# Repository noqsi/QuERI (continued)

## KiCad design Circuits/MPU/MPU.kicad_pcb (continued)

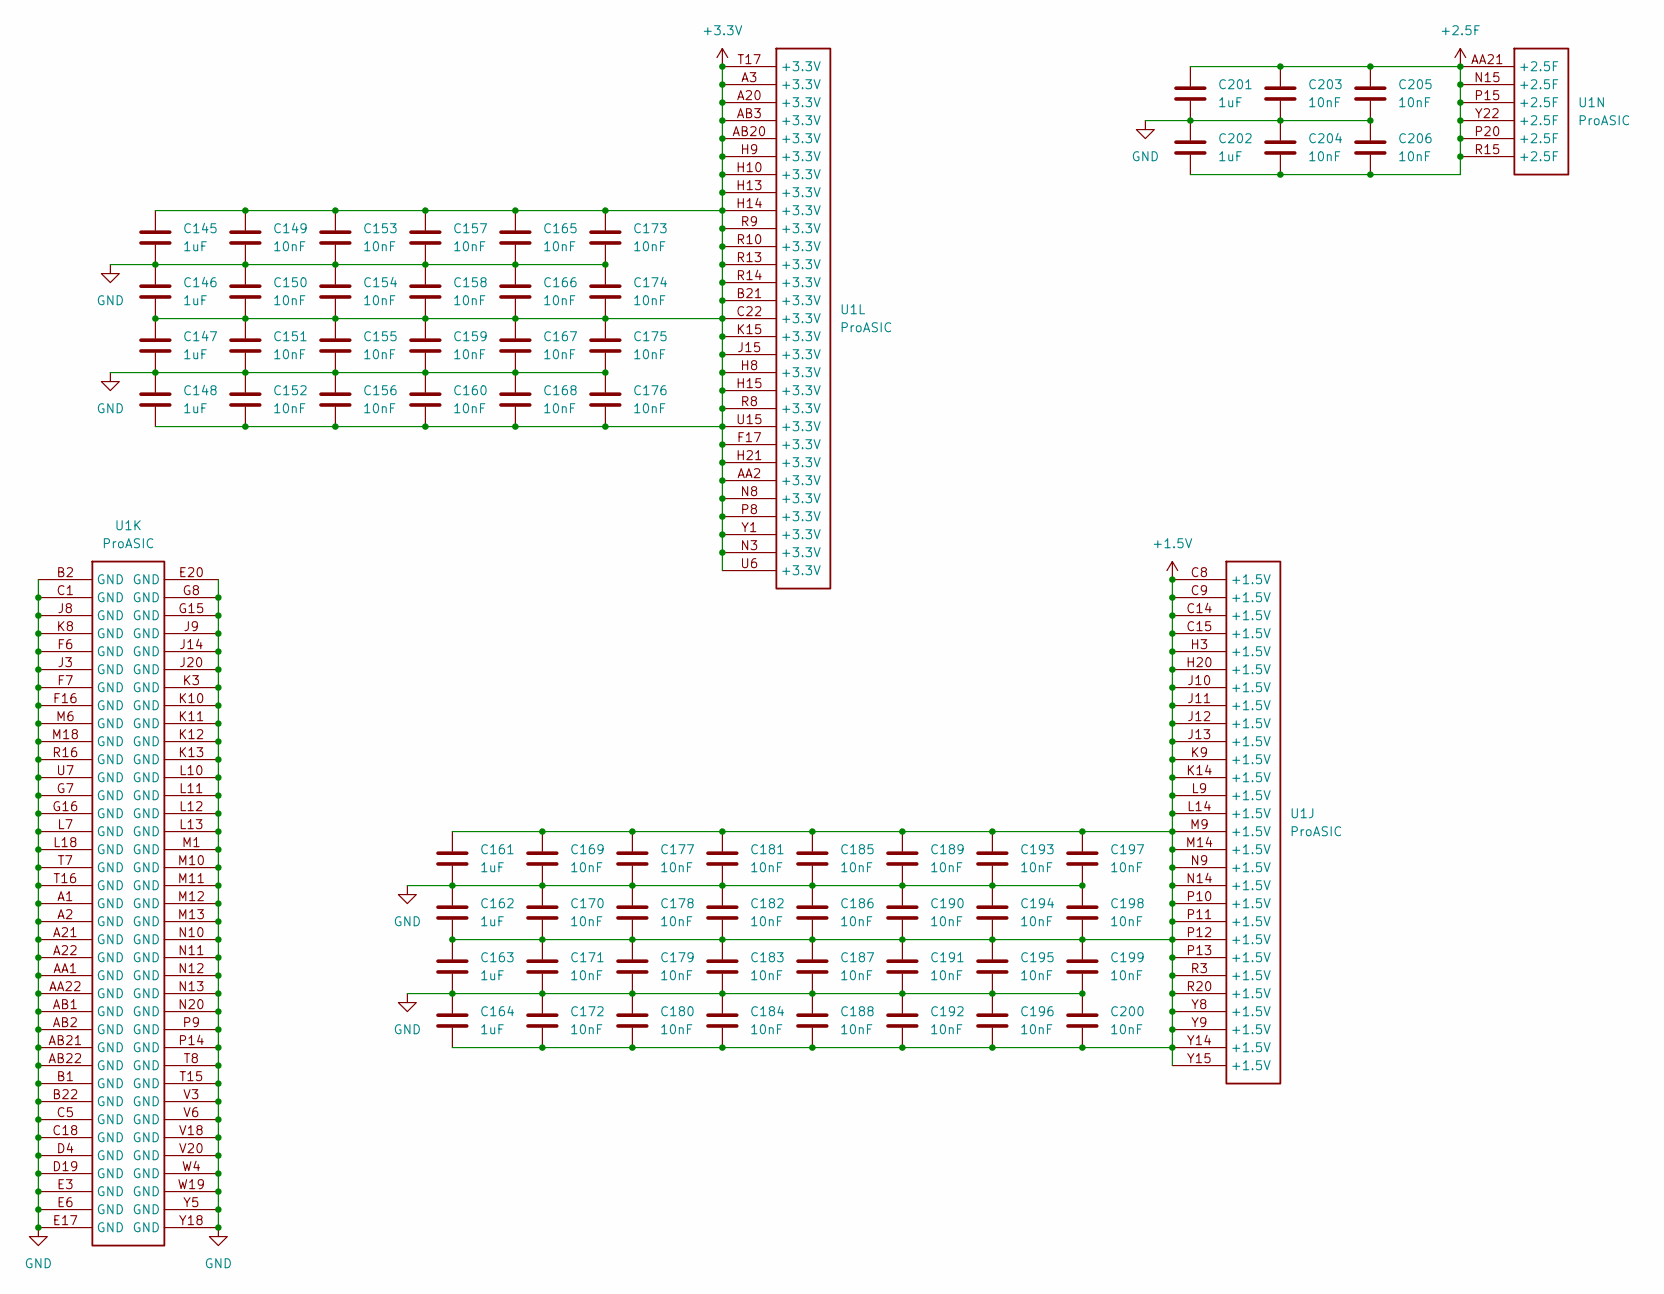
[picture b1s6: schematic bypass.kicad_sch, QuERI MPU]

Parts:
C145, C146, C147, C148, C161, C162, C163, C164, C201, C202: 1uF; C_0805_2012Metric
C149, C150, C151, C152, C153, C154, C155, C156, C157, C158, C159, C160, C165, C166, C167, C168, C169, C170, C171, C172, C173, C174, C175, C176, C177, C178, C179, C180, C181, C182, C183, C184, C185, C186, C187, C188, C189, C190, C191, C192, C193, C194, C195, C196, C197, C198, C199, C200, C203, C204, C205, C206: 10nF; C_0603_1608Metric
U1: ProASIC; BGA-484_23.0x23.0mm_Layout22x22_P1.0mm

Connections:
+1.5V: C161.1, C162.2, C163.1, C164.2, C169.1, C170.2, C171.1, C172.2, C177.1, C178.2, C179.1, C180.2, C181.1, C182.2, C183.1, C184.2, C185.1, C186.2, C187.1, C188.2, C189.1, C190.2, C191.1, C192.2, C193.1, C194.2, C195.1, C196.2, C197.1, C198.2, C199.1, C200.2, U1.C8 (+1.5V), U1.C9 (+1.5V), U1.C14 (+1.5V), U1.C15 (+1.5V), U1.H3 (+1.5V), U1.H20 (+1.5V), U1.J10 (+1.5V), U1.J11 (+1.5V), U1.J12 (+1.5V), U1.J13 (+1.5V), U1.K9 (+1.5V), U1.K14 (+1.5V), U1.L9 (+1.5V), U1.L14 (+1.5V), U1.M9 (+1.5V), U1.M14 (+1.5V), U1.N9 (+1.5V), U1.N14 (+1.5V), U1.P10 (+1.5V), U1.P11 (+1.5V), U1.P12 (+1.5V), U1.P13 (+1.5V), U1.R3 (+1.5V), U1.R20 (+1.5V), U1.Y8 (+1.5V), U1.Y9 (+1.5V), U1.Y14 (+1.5V), U1.Y15 (+1.5V); also elsewhere on the board
+2.5F: C201.1, C202.2, C203.1, C204.2, C205.1, C206.2, U1.AA21 (+2.5F), U1.N15 (+2.5F), U1.P15 (+2.5F), U1.P20 (+2.5F), U1.R15 (+2.5F), U1.Y22 (+2.5F); also elsewhere on the board
+3.3V: C145.1, C146.2, C147.1, C148.2, C149.1, C150.2, C151.1, C152.2, C153.1, C154.2, C155.1, C156.2, C157.1, C158.2, C159.1, C160.2, C165.1, C166.2, C167.1, C168.2, C173.1, C174.2, C175.1, C176.2, U1.A3 (+3.3V), U1.A20 (+3.3V), U1.AA2 (+3.3V), U1.AB3 (+3.3V), U1.AB20 (+3.3V), U1.B21 (+3.3V), U1.C22 (+3.3V), U1.F17 (+3.3V), U1.H8 (+3.3V), U1.H9 (+3.3V), U1.H10 (+3.3V), U1.H13 (+3.3V), U1.H14 (+3.3V), U1.H15 (+3.3V), U1.H21 (+3.3V), U1.J15 (+3.3V), U1.K15 (+3.3V), U1.N3 (+3.3V), U1.N8 (+3.3V), U1.P8 (+3.3V), U1.R8 (+3.3V), U1.R9 (+3.3V), U1.R10 (+3.3V), U1.R13 (+3.3V), U1.R14 (+3.3V), U1.T17 (+3.3V), U1.U6 (+3.3V), U1.U15 (+3.3V), U1.Y1 (+3.3V); also elsewhere on the board
GND: C145.2, C146.1, C147.2, C148.1, C149.2, C150.1, C151.2, C152.1, C153.2, C154.1, C155.2, C156.1, C157.2, C158.1, C159.2, C160.1, C161.2, C162.1, C163.2, C164.1, C165.2, C166.1, C167.2, C168.1, C169.2, C170.1, C171.2, C172.1, C173.2, C174.1, C175.2, C176.1, C177.2, C178.1, C179.2, C180.1, C181.2, C182.1, C183.2, C184.1, C185.2, C186.1, C187.2, C188.1, C189.2, C190.1, C191.2, C192.1, C193.2, C194.1, C195.2, C196.1, C197.2, C198.1, C199.2, C200.1, C201.2, C202.1, C203.2, C204.1, C205.2, C206.1, U1.A1 (GND), U1.A2 (GND), U1.A21 (GND), U1.A22 (GND), U1.AA1 (GND), U1.AA22 (GND), U1.AB1 (GND), U1.AB2 (GND), U1.AB21 (GND), U1.AB22 (GND), U1.B1 (GND), U1.B2 (GND), U1.B22 (GND), U1.C1 (GND), U1.C5 (GND), U1.C18 (GND), U1.D4 (GND), U1.D19 (GND), U1.E3 (GND), U1.E6 (GND), U1.E17 (GND), U1.E20 (GND), U1.F6 (GND), U1.F7 (GND), U1.F16 (GND), U1.G7 (GND), U1.G8 (GND), U1.G15 (GND), U1.G16 (GND), U1.J3 (GND), U1.J8 (GND), U1.J9 (GND), U1.J14 (GND), U1.J20 (GND), U1.K3 (GND), U1.K8 (GND), U1.K10 (GND), U1.K11 (GND), U1.K12 (GND), U1.K13 (GND), U1.L7 (GND), U1.L10 (GND), U1.L11 (GND), U1.L12 (GND), U1.L13 (GND), U1.L18 (GND), U1.M1 (GND), U1.M6 (GND), U1.M10 (GND), U1.M11 (GND), U1.M12 (GND), U1.M13 (GND), U1.M18 (GND), U1.N10 (GND), U1.N11 (GND), U1.N12 (GND), U1.N13 (GND), U1.N20 (GND), U1.P9 (GND), U1.P14 (GND), U1.R16 (GND), U1.T7 (GND), U1.T8 (GND), U1.T15 (GND), U1.T16 (GND), U1.U7 (GND), U1.V3 (GND), U1.V6 (GND), U1.V18 (GND), U1.V20 (GND), U1.W4 (GND), U1.W19 (GND), U1.Y5 (GND), U1.Y18 (GND); also elsewhere on the board

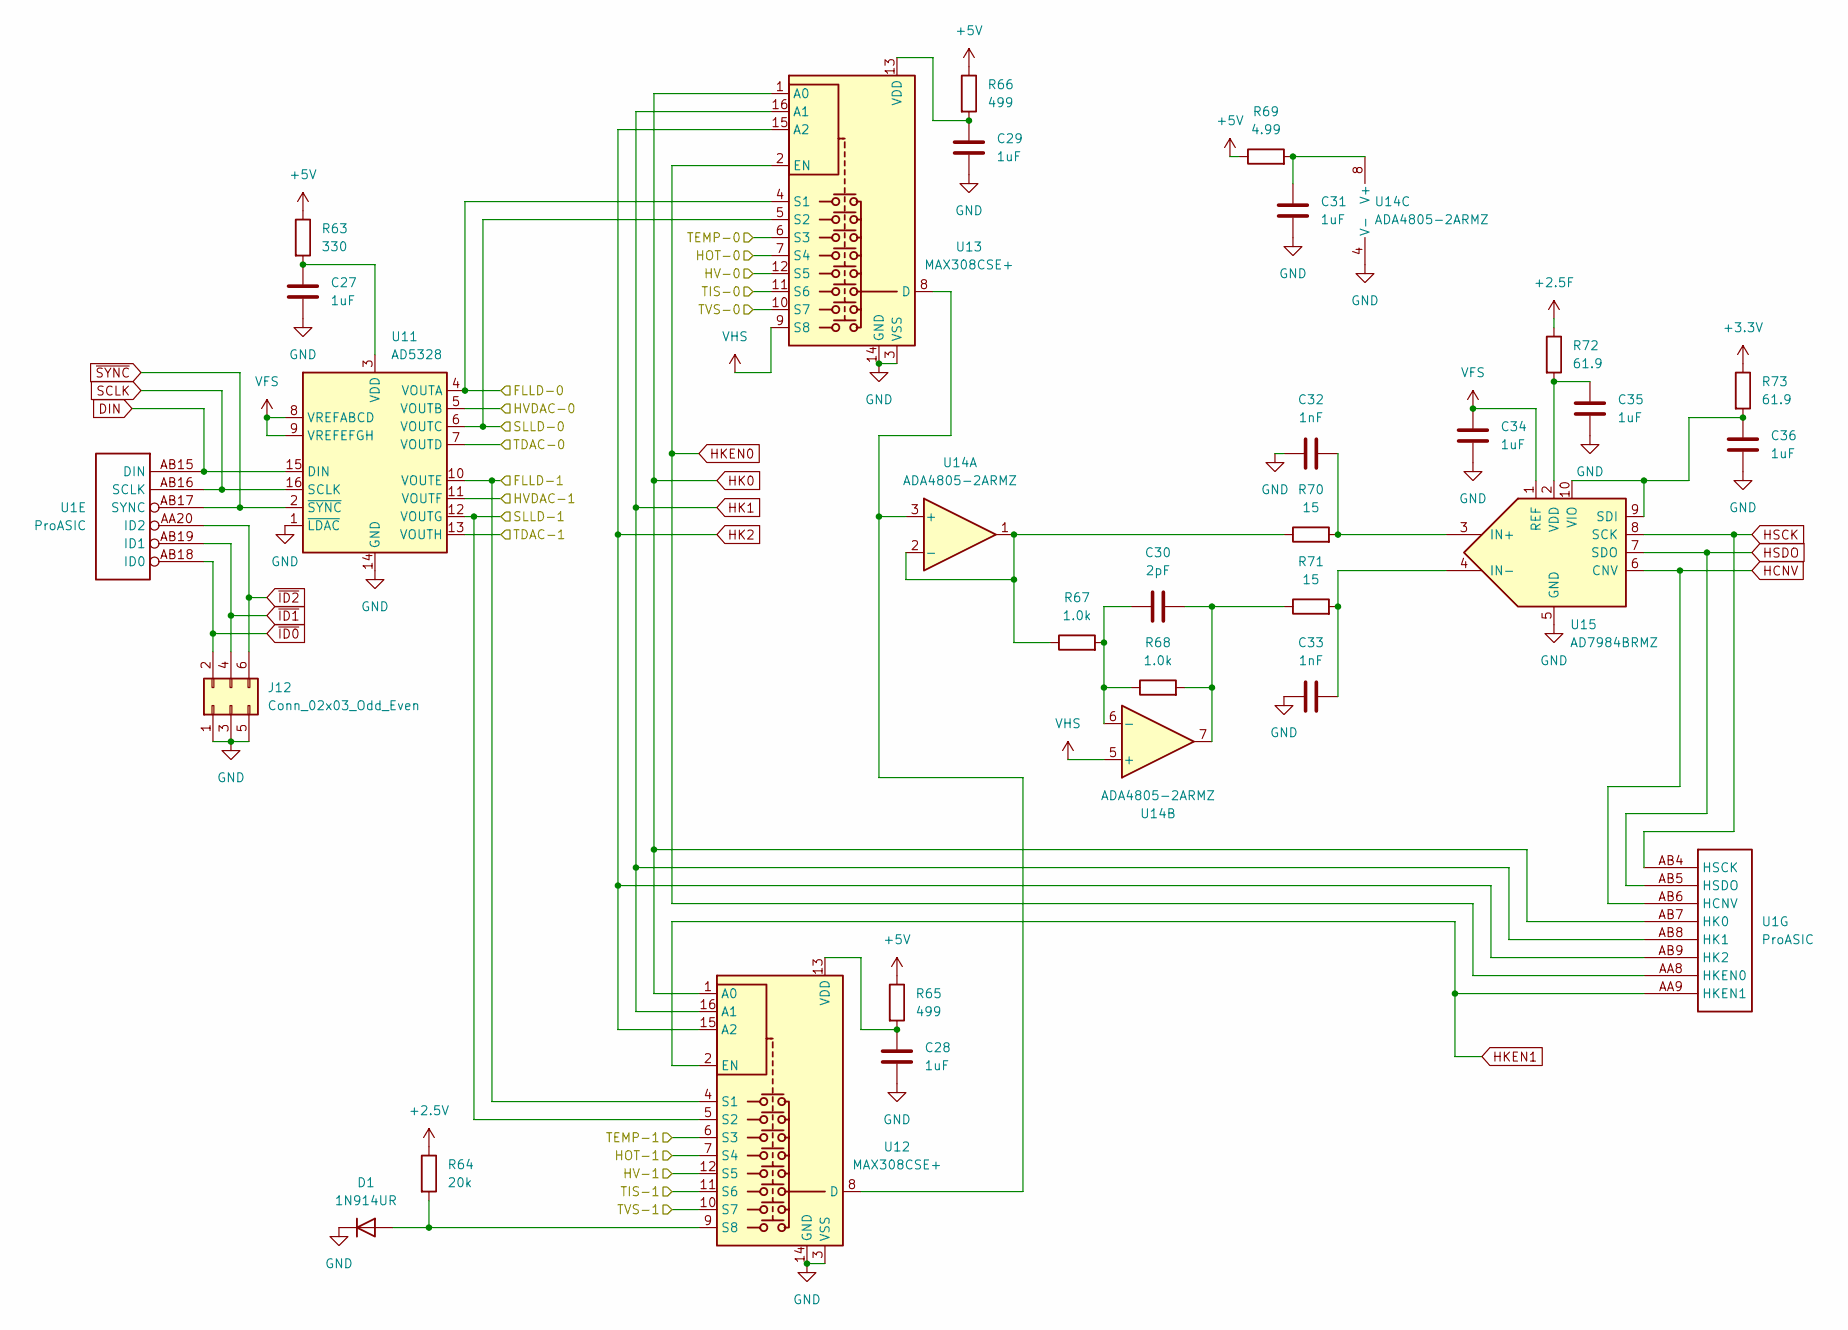
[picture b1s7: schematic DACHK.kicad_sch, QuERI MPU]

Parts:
C27, C28, C29, C31, C34, C35, C36: 1uF; C_0805_2012Metric
C30: 2pF; C_0603_1608Metric
C32, C33: 1nF; C_0603_1608Metric
D1: 1N914UR; D_MiniMELF
J12: Conn_02x03_Odd_Even; PinHeader_2x03_P2.54mm_Vertical
R63: 330; R_0603_1608Metric
R64: 20k; R_0603_1608Metric
R65, R66: 499; R_0603_1608Metric
R67, R68: 1.0k; R_0603_1608Metric
R69: 4.99; R_0603_1608Metric
R70, R71: 15; R_0603_1608Metric
R72, R73: 61.9; R_0603_1608Metric
U1: ProASIC; BGA-484_23.0x23.0mm_Layout22x22_P1.0mm
U11: AD5328; TSSOP-16_4.4x5mm_P0.65mm
U12, U13: MAX308CSE+; SO-16_3.9x9.9mm_P1.27mm
U14: ADA4805-2ARMZ; MSOP-8_3x3mm_P0.65mm
U15: AD7984BRMZ; MSOP-10_3x3mm_P0.5mm

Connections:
+2.5F: R72.1; also elsewhere on the board
+2.5V: R64.1; also elsewhere on the board
+3.3V: R73.1; also elsewhere on the board
+5V: R63.1, R65.1, R66.1, R69.1; also elsewhere on the board
/DAC and Housekeeping/FLLD-0: U11.4 (VOUTA), U13.4 (S1); also elsewhere on the board
/DAC and Housekeeping/FLLD-1: U11.10 (VOUTE), U12.4 (S1); also elsewhere on the board
/DAC and Housekeeping/HOT-0: U13.7 (S4); also elsewhere on the board
/DAC and Housekeeping/HOT-1: U12.7 (S4); also elsewhere on the board
/DAC and Housekeeping/HV-0: U13.12 (S5); also elsewhere on the board
/DAC and Housekeeping/HV-1: U12.12 (S5); also elsewhere on the board
/DAC and Housekeeping/HVDAC-0: U11.5 (VOUTB); also elsewhere on the board
/DAC and Housekeeping/HVDAC-1: U11.11 (VOUTF); also elsewhere on the board
/DAC and Housekeeping/SLLD-0: U11.6 (VOUTC), U13.5 (S2); also elsewhere on the board
/DAC and Housekeeping/SLLD-1: U11.12 (VOUTG), U12.5 (S2); also elsewhere on the board
/DAC and Housekeeping/TDAC-0: U11.7 (VOUTD); also elsewhere on the board
/DAC and Housekeeping/TDAC-1: U11.13 (VOUTH); also elsewhere on the board
/DAC and Housekeeping/TEMP-0: U13.6 (S3); also elsewhere on the board
/DAC and Housekeeping/TEMP-1: U12.6 (S3); also elsewhere on the board
/DAC and Housekeeping/TIS-0: U13.11 (S6); also elsewhere on the board
/DAC and Housekeeping/TIS-1: U12.11 (S6); also elsewhere on the board
/DAC and Housekeeping/TVS-0: U13.10 (S7); also elsewhere on the board
/DAC and Housekeeping/TVS-1: U12.10 (S7); also elsewhere on the board
DIN: U1.AB15 (DIN), U11.15 (DIN)
GND: C27.2, C28.2, C29.2, C31.2, C32.1, C33.1, C34.2, C35.2, C36.2, D1.1 (K), J12.1, J12.3, J12.5, U11.1 (~LDAC), U11.14 (GND), U12.3 (VSS), U12.14 (GND), U13.3 (VSS), U13.14 (GND), U14.4 (V-), U15.5 (GND); also elsewhere on the board
HCNV: U1.AB6 (HCNV), U15.6 (CNV)
HK0: U1.AB7 (HK0), U12.1 (A0), U13.1 (A0)
HK1: U1.AB8 (HK1), U12.16 (A1), U13.16 (A1)
HK2: U1.AB9 (HK2), U12.15 (A2), U13.15 (A2)
HKEN0: U1.AA8 (HKEN0), U13.2 (EN)
HKEN1: U1.AA9 (HKEN1), U12.2 (EN)
HSCK: U1.AB4 (HSCK), U15.8 (SCK)
HSDO: U1.AB5 (HSDO), U15.7 (SDO)
unnamed: C30.2, R68.2, R71.1, U14.7
unnamed: D1.2 (A), R64.2, U12.9 (S8)
unnamed: C27.1, R63.2, U11.3 (VDD)
unnamed: U12.8 (D), U13.8 (D), U14.3 (+)
unnamed: C28.1, R65.2, U12.13 (VDD)
unnamed: C29.1, R66.2, U13.13 (VDD)
unnamed: R67.1, R70.1, U14.1, U14.2 (-)
unnamed: C30.1, R67.2, R68.1, U14.6 (-)
unnamed: C31.1, R69.2, U14.8 (V+)
unnamed: C32.2, R70.2, U15.3 (IN+)
unnamed: C33.2, R71.2, U15.4 (IN-)
unnamed: C36.1, R73.2, U15.9 (SDI), U15.10 (VIO)
unnamed: C35.1, R72.2, U15.2 (VDD)
SCLK: U1.AB16 (SCLK), U11.16 (SCLK)
VFS: C34.1, U11.8 (VREFABCD), U11.9 (VREFEFGH), U15.1 (REF); also elsewhere on the board
VHS: U13.9 (S8), U14.5 (+); also elsewhere on the board
~ID0: J12.2, U1.AB18 (ID0)
~ID1: J12.4, U1.AB19 (ID1)
~ID2: J12.6, U1.AA20 (ID2)
~SYNC: U1.AB17 (SYNC), U11.2 (~SYNC)

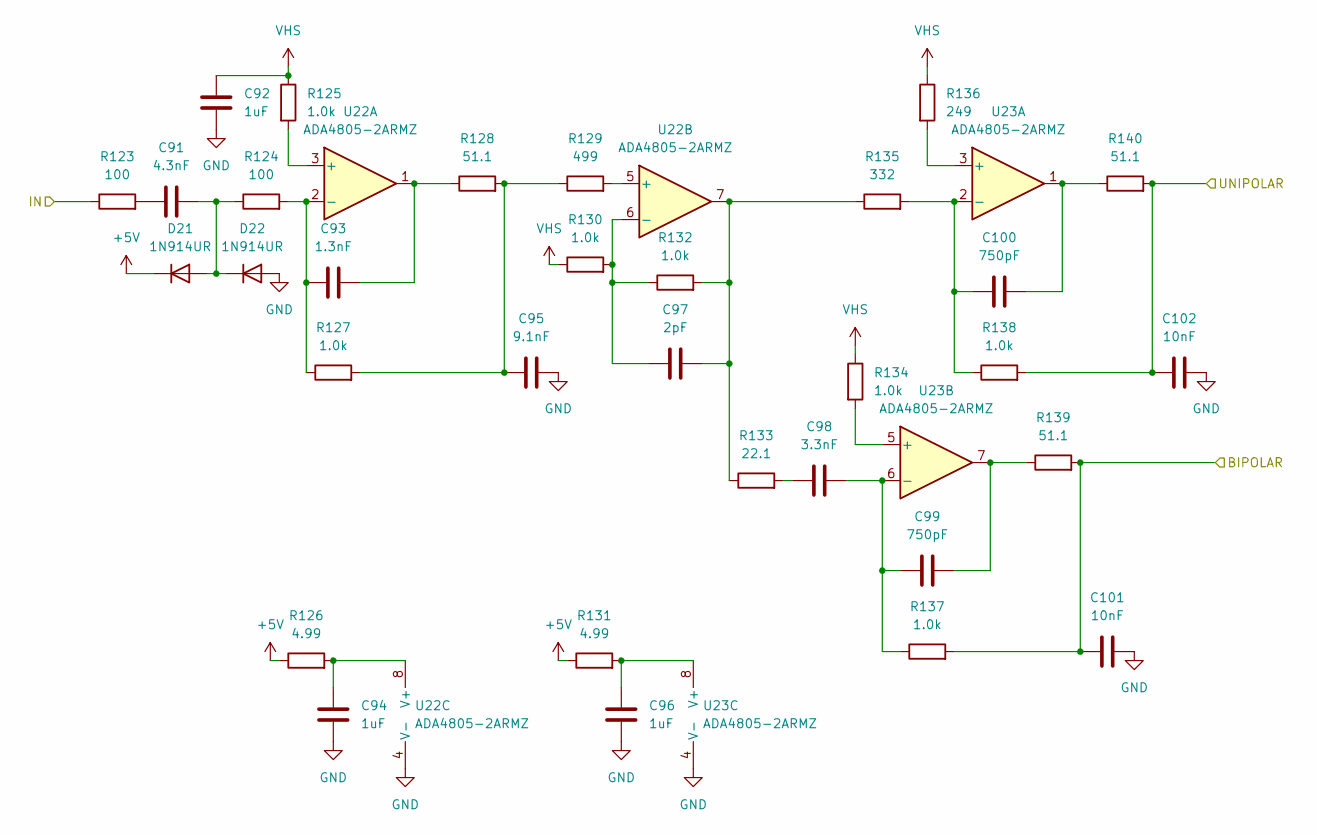
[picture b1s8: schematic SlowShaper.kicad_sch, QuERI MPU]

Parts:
C91: 4.3nF; C_0603_1608Metric
C92, C94, C96: 1uF; C_0805_2012Metric
C93: 1.3nF; C_0603_1608Metric
C95: 9.1nF; C_0603_1608Metric
C97: 2pF; C_0603_1608Metric
C98: 3.3nF; C_0603_1608Metric
C99, C100: 750pF; C_0603_1608Metric
C101, C102: 10nF; C_0603_1608Metric
D21, D22: 1N914UR; D_MiniMELF
R123, R124: 100; R_0603_1608Metric
R125, R127, R130, R132, R134, R137, R138: 1.0k; R_0603_1608Metric
R126, R131: 4.99; R_0603_1608Metric
R128, R139, R140: 51.1; R_0603_1608Metric
R129: 499; R_0603_1608Metric
R133: 22.1; R_0603_1608Metric
R135: 332; R_0603_1608Metric
R136: 249; R_0603_1608Metric
U22, U23: ADA4805-2ARMZ; MSOP-8_3x3mm_P0.65mm

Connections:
+5V: D21.1 (K), R126.1, R131.1; also elsewhere on the board
/PerFPM-0/Fast Shaper/IN: R123.1; also elsewhere on the board
/PerFPM-0/Slow Pulse Capture/BIPOLAR: C101.1, R137.2, R139.2; also elsewhere on the board
/PerFPM-0/Slow Pulse Capture/UNIPOLAR: C102.1, R138.2, R140.2; also elsewhere on the board
GND: C92.2, C94.2, C95.2, C96.2, C101.2, C102.2, D22.2 (A), U22.4 (V-), U23.4 (V-); also elsewhere on the board
unnamed: C91.1, R123.2
unnamed: C93.2, R128.1, U22.1
unnamed: C95.1, R127.2, R128.2, R129.1
unnamed: C97.2, R132.2, R133.1, R135.1, U22.7
unnamed: C98.1, R133.2
unnamed: C99.2, R139.1, U23.7
unnamed: C100.2, R140.1, U23.1
unnamed: C91.2, D21.2 (A), D22.1 (K), R124.1
unnamed: R125.2, U22.3 (+)
unnamed: C93.1, R124.2, R127.1, U22.2 (-)
unnamed: R129.2, U22.5 (+)
unnamed: C97.1, R130.2, R132.1, U22.6 (-)
unnamed: C94.1, R126.2, U22.8 (V+)
unnamed: R136.2, U23.3 (+)
unnamed: C100.1, R135.2, R138.1, U23.2 (-)
unnamed: R134.2, U23.5 (+)
unnamed: C98.2, C99.1, R137.1, U23.6 (-)
unnamed: C96.1, R131.2, U23.8 (V+)
VHS: C92.1, R125.1, R130.1, R134.1, R136.1; also elsewhere on the board

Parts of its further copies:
C103: 4.3nF; C_0603_1608Metric
C104, C106, C108: 1uF; C_0805_2012Metric
C105: 1.3nF; C_0603_1608Metric
C107: 9.1nF; C_0603_1608Metric
C109: 2pF; C_0603_1608Metric
C110: 3.3nF; C_0603_1608Metric
C111, C112: 750pF; C_0603_1608Metric
C113, C114: 10nF; C_0603_1608Metric
D23, D24: 1N914UR; D_MiniMELF
R141, R142: 100; R_0603_1608Metric
R143, R145, R148, R150, R152, R155, R156: 1.0k; R_0603_1608Metric
R144, R149: 4.99; R_0603_1608Metric
R146, R157, R158: 51.1; R_0603_1608Metric
R147: 499; R_0603_1608Metric
R151: 22.1; R_0603_1608Metric
R153: 332; R_0603_1608Metric
R154: 249; R_0603_1608Metric
U24, U25: ADA4805-2ARMZ; MSOP-8_3x3mm_P0.65mm

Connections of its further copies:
+5V: D23.1 (K), R144.1, R149.1; also elsewhere on the board
/PerFPM-1/Fast Shaper/IN: R141.1; also elsewhere on the board
/PerFPM-1/Slow Pulse Capture/BIPOLAR: C113.1, R155.2, R157.2; also elsewhere on the board
/PerFPM-1/Slow Pulse Capture/UNIPOLAR: C114.1, R156.2, R158.2; also elsewhere on the board
GND: C104.2, C106.2, C107.2, C108.2, C113.2, C114.2, D24.2 (A), U24.4 (V-), U25.4 (V-); also elsewhere on the board
unnamed: C103.1, R141.2
unnamed: C105.2, R146.1, U24.1
unnamed: C107.1, R145.2, R146.2, R147.1
unnamed: C109.2, R150.2, R151.1, R153.1, U24.7
unnamed: C110.1, R151.2
unnamed: C111.2, R157.1, U25.7
unnamed: C112.2, R158.1, U25.1
unnamed: C103.2, D23.2 (A), D24.1 (K), R142.1
unnamed: R143.2, U24.3 (+)
unnamed: C105.1, R142.2, R145.1, U24.2 (-)
unnamed: R147.2, U24.5 (+)
unnamed: C109.1, R148.2, R150.1, U24.6 (-)
unnamed: C106.1, R144.2, U24.8 (V+)
unnamed: R154.2, U25.3 (+)
unnamed: C112.1, R153.2, R156.1, U25.2 (-)
unnamed: R152.2, U25.5 (+)
unnamed: C110.2, C111.1, R155.1, U25.6 (-)
unnamed: C108.1, R149.2, U25.8 (V+)
VHS: C104.1, R143.1, R148.1, R152.1, R154.1; also elsewhere on the board

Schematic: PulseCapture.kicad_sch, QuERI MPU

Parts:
C125, C126, C127, C131, C132, C133, C134: 1uF; C_0805_2012Metric
C128: 2pF; C_0603_1608Metric
C129, C130: 1nF; C_0603_1608Metric
R170, R171, R173: 4.99; R_0603_1608Metric
R172, R174: 1.0k; R_0603_1608Metric
R175, R176: 15; R_0603_1608Metric
R177: 10; R_0603_1608Metric
R178, R180: 61.9; R_0603_1608Metric
R179: 3.32k; R_0603_1608Metric
U29: LT1715; MSOP-10_3x3mm_P0.5mm
U30: ADA4805-2ARMZ; MSOP-8_3x3mm_P0.65mm
U31: AD7984BRMZ; MSOP-10_3x3mm_P0.5mm

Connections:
+3.3V: R171.1, R180.1; also elsewhere on the board
+5V: R170.1, R173.1; also elsewhere on the board
/DAC and Housekeeping/FLLD-0: U29.3 (-); also elsewhere on the board
/FCNV-0: U31.6 (CNV); also elsewhere on the board
/FSCK-0: U31.8 (SCK); also elsewhere on the board
/FSDO-0: U31.7 (SDO); also elsewhere on the board
/FTRIG-0: U29.7; also elsewhere on the board
/FZX-0: R179.2, U29.8; also elsewhere on the board
/PerFPM-0/Fast Pulse Capture/+2.5V: R178.1; also elsewhere on the board
/PerFPM-0/Fast Pulse Capture/BIPOLAR: U29.2 (-); also elsewhere on the board
/PerFPM-0/Fast Pulse Capture/UNIPOLAR: U30.3 (+); also elsewhere on the board
GND: C125.2, C126.2, C127.2, C129.1, C130.1, C131.2, C132.2, C133.2, C134.2, U29.5 (Vee), U29.6 (GND), U30.4 (V-), U31.5 (GND); also elsewhere on the board
unnamed: C128.2, R174.2, R176.1, U30.7
unnamed: R177.2, R179.1, U29.1 (+)
unnamed: R172.1, R175.1, U29.4 (+), U30.1, U30.2 (-)
unnamed: C126.1, R171.2, U29.9 (+VS)
unnamed: C125.1, R170.2, U29.10 (Vcc)
unnamed: C128.1, R172.2, R174.1, U30.6 (-)
unnamed: C127.1, R173.2, U30.8 (V+)
unnamed: C129.2, R175.2, U31.3 (IN+)
unnamed: C130.2, R176.2, U31.4 (IN-)
unnamed: C134.1, R180.2, U31.9 (SDI), U31.10 (VIO)
unnamed: C133.1, R178.2, U31.2 (VDD)
VFS: C132.1, U31.1 (REF); also elsewhere on the board
VHS: C131.1, R177.1, U30.5 (+); also elsewhere on the board

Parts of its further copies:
C115, C116, C117, C121, C122, C123, C124, C135, C136, C137, C141, C142, C143, C144, C219, C220, C221, C225, C226, C227, C228: 1uF; C_0805_2012Metric
C118, C138, C222: 2pF; C_0603_1608Metric
C119, C120, C139, C140, C223, C224: 1nF; C_0603_1608Metric
R159, R160, R162, R181, R182, R184, R210, R211, R213: 4.99; R_0603_1608Metric
R161, R163, R183, R185, R212, R214: 1.0k; R_0603_1608Metric
R164, R165, R186, R187, R215, R216: 15; R_0603_1608Metric
R166, R188, R217: 10; R_0603_1608Metric
R167, R169, R189, R191, R218, R220: 61.9; R_0603_1608Metric
R168, R190, R219: 3.32k; R_0603_1608Metric
U26, U32, U37: LT1715; MSOP-10_3x3mm_P0.5mm
U27, U33, U38: ADA4805-2ARMZ; MSOP-8_3x3mm_P0.65mm
U28, U34, U39: AD7984BRMZ; MSOP-10_3x3mm_P0.5mm

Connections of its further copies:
+3.3V: R160.1, R169.1, R182.1, R191.1, R211.1, R220.1; also elsewhere on the board
+5V: R159.1, R162.1, R181.1, R184.1, R210.1, R213.1; also elsewhere on the board
/DAC and Housekeeping/FLLD-1: U37.3 (-); also elsewhere on the board
/DAC and Housekeeping/SLLD-0: U26.3 (-); also elsewhere on the board
/DAC and Housekeeping/SLLD-1: U32.3 (-); also elsewhere on the board
/FCNV-1: U39.6 (CNV); also elsewhere on the board
/FSCK-1: U39.8 (SCK); also elsewhere on the board
/FSDO-1: U39.7 (SDO); also elsewhere on the board
/FTRIG-1: U37.7; also elsewhere on the board
/FZX-1: R219.2, U37.8; also elsewhere on the board
/PerFPM-0/Fast Pulse Capture/+2.5V: R167.1; also elsewhere on the board
/PerFPM-0/Slow Pulse Capture/BIPOLAR: U26.2 (-); also elsewhere on the board
/PerFPM-0/Slow Pulse Capture/UNIPOLAR: U27.3 (+); also elsewhere on the board
/PerFPM-1/Fast Pulse Capture/+2.5V: R189.1, R218.1; also elsewhere on the board
/PerFPM-1/Fast Pulse Capture/BIPOLAR: U37.2 (-); also elsewhere on the board
/PerFPM-1/Fast Pulse Capture/UNIPOLAR: U38.3 (+); also elsewhere on the board
/PerFPM-1/Slow Pulse Capture/BIPOLAR: U32.2 (-); also elsewhere on the board
/PerFPM-1/Slow Pulse Capture/UNIPOLAR: U33.3 (+); also elsewhere on the board
/SCNV-0: U28.6 (CNV); also elsewhere on the board
/SCNV-1: U34.6 (CNV); also elsewhere on the board
/SSCK-0: U28.8 (SCK); also elsewhere on the board
/SSCK-1: U34.8 (SCK); also elsewhere on the board
/SSDO-0: U28.7 (SDO); also elsewhere on the board
/SSDO-1: U34.7 (SDO); also elsewhere on the board
/STRIG-0: U26.7; also elsewhere on the board
/STRIG-1: U32.7; also elsewhere on the board
/SZX-0: R168.2, U26.8; also elsewhere on the board
/SZX-1: R190.2, U32.8; also elsewhere on the board
GND: C115.2, C116.2, C117.2, C119.1, C120.1, C121.2, C122.2, C123.2, C124.2, C135.2, C136.2, C137.2, C139.1, C140.1, C141.2, C142.2, C143.2, C144.2, C219.2, C220.2, C221.2, C223.1, C224.1, C225.2, C226.2, C227.2, C228.2, U26.5 (Vee), U26.6 (GND), U27.4 (V-), U28.5 (GND), U32.5 (Vee), U32.6 (GND), U33.4 (V-), U34.5 (GND), U37.5 (Vee), U37.6 (GND), U38.4 (V-), U39.5 (GND); also elsewhere on the board
unnamed: C118.2, R163.2, R165.1, U27.7
unnamed: C138.2, R185.2, R187.1, U33.7
unnamed: C222.2, R214.2, R216.1, U38.7
unnamed: R166.2, R168.1, U26.1 (+)
unnamed: R161.1, R164.1, U26.4 (+), U27.1, U27.2 (-)
unnamed: C116.1, R160.2, U26.9 (+VS)
unnamed: C115.1, R159.2, U26.10 (Vcc)
unnamed: C118.1, R161.2, R163.1, U27.6 (-)
unnamed: C117.1, R162.2, U27.8 (V+)
unnamed: C119.2, R164.2, U28.3 (IN+)
unnamed: C120.2, R165.2, U28.4 (IN-)
unnamed: C124.1, R169.2, U28.9 (SDI), U28.10 (VIO)
unnamed: C123.1, R167.2, U28.2 (VDD)
unnamed: R188.2, R190.1, U32.1 (+)
unnamed: R183.1, R186.1, U32.4 (+), U33.1, U33.2 (-)
unnamed: C136.1, R182.2, U32.9 (+VS)
unnamed: C135.1, R181.2, U32.10 (Vcc)
unnamed: C138.1, R183.2, R185.1, U33.6 (-)
unnamed: C137.1, R184.2, U33.8 (V+)
unnamed: C139.2, R186.2, U34.3 (IN+)
unnamed: C140.2, R187.2, U34.4 (IN-)
unnamed: C144.1, R191.2, U34.9 (SDI), U34.10 (VIO)
unnamed: C143.1, R189.2, U34.2 (VDD)
unnamed: R217.2, R219.1, U37.1 (+)
unnamed: R212.1, R215.1, U37.4 (+), U38.1, U38.2 (-)
unnamed: C220.1, R211.2, U37.9 (+VS)
unnamed: C219.1, R210.2, U37.10 (Vcc)
unnamed: C222.1, R212.2, R214.1, U38.6 (-)
unnamed: C221.1, R213.2, U38.8 (V+)
unnamed: C223.2, R215.2, U39.3 (IN+)
unnamed: C224.2, R216.2, U39.4 (IN-)
unnamed: C228.1, R220.2, U39.9 (SDI), U39.10 (VIO)
unnamed: C227.1, R218.2, U39.2 (VDD)
VFS: C122.1, C142.1, C226.1, U28.1 (REF), U34.1 (REF), U39.1 (REF); also elsewhere on the board
VHS: C121.1, C141.1, C225.1, R166.1, R188.1, R217.1, U27.5 (+), U33.5 (+), U38.5 (+); also elsewhere on the board

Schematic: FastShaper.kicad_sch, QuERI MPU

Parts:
C79: 180pF; C_0603_1608Metric
C80, C82, C84: 1uF; C_0805_2012Metric
C81: 75pF; C_0603_1608Metric
C83: 510pF; C_0603_1608Metric
C85: 2pF; C_0603_1608Metric
C86: 160pF; C_0603_1608Metric
C87, C88: 47pF; C_0603_1608Metric
C89: 360pF; C_0603_1608Metric
C90: 560pF; C_0603_1608Metric
D19, D20: 1N914UR; D_MiniMELF
R105, R106: 100; R_0603_1608Metric
R107, R109, R114, R116, R119, R120: 1.0k; R_0603_1608Metric
R108, R113: 4.99; R_0603_1608Metric
R110, R121, R122: 51.1; R_0603_1608Metric
R111: 232; R_0603_1608Metric
R112: 301; R_0603_1608Metric
R115: 22.1; R_0603_1608Metric
R117: 499; R_0603_1608Metric
R118: 332; R_0603_1608Metric
U20, U21: ADA4805-2ARMZ; MSOP-8_3x3mm_P0.65mm

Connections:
+5V: D19.1 (K), R108.1, R113.1; also elsewhere on the board
/PerFPM-0/Fast Pulse Capture/BIPOLAR: C89.1, R119.2, R121.2; also elsewhere on the board
/PerFPM-0/Fast Pulse Capture/UNIPOLAR: C90.1, R120.2, R122.2; also elsewhere on the board
/PerFPM-0/Fast Shaper/IN: R105.1; also elsewhere on the board
GND: C80.2, C82.2, C83.2, C84.2, C89.2, C90.2, D20.2 (A), U20.4 (V-), U21.4 (V-); also elsewhere on the board
unnamed: C79.1, R105.2
unnamed: C81.2, R110.1, U20.1
unnamed: C83.1, R109.2, R110.2, R111.1
unnamed: C85.2, R114.2, R115.1, R117.1, U20.7
unnamed: C86.1, R115.2
unnamed: C87.2, R121.1, U21.7
unnamed: C88.2, R122.1, U21.1
unnamed: C79.2, D19.2 (A), D20.1 (K), R106.1
unnamed: R107.2, U20.3 (+)
unnamed: C81.1, R106.2, R109.1, U20.2 (-)
unnamed: R111.2, U20.5 (+)
unnamed: C85.1, R112.2, R114.1, U20.6 (-)
unnamed: C82.1, R108.2, U20.8 (V+)
unnamed: R118.2, U21.3 (+)
unnamed: C88.1, R117.2, R120.1, U21.2 (-)
unnamed: R116.2, U21.5 (+)
unnamed: C86.2, C87.1, R119.1, U21.6 (-)
unnamed: C84.1, R113.2, U21.8 (V+)
VHS: C80.1, R107.1, R112.1, R116.1, R118.1; also elsewhere on the board

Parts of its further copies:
C207: 180pF; C_0603_1608Metric
C208, C210, C212: 1uF; C_0805_2012Metric
C209: 75pF; C_0603_1608Metric
C211: 510pF; C_0603_1608Metric
C213: 2pF; C_0603_1608Metric
C214: 160pF; C_0603_1608Metric
C215, C216: 47pF; C_0603_1608Metric
C217: 360pF; C_0603_1608Metric
C218: 560pF; C_0603_1608Metric
D25, D26: 1N914UR; D_MiniMELF
R192, R193: 100; R_0603_1608Metric
R194, R196, R201, R203, R206, R207: 1.0k; R_0603_1608Metric
R195, R200: 4.99; R_0603_1608Metric
R197, R208, R209: 51.1; R_0603_1608Metric
R198: 232; R_0603_1608Metric
R199: 301; R_0603_1608Metric
R202: 22.1; R_0603_1608Metric
R204: 499; R_0603_1608Metric
R205: 332; R_0603_1608Metric
U35, U36: ADA4805-2ARMZ; MSOP-8_3x3mm_P0.65mm

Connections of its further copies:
+5V: D25.1 (K), R195.1, R200.1; also elsewhere on the board
/PerFPM-1/Fast Pulse Capture/BIPOLAR: C217.1, R206.2, R208.2; also elsewhere on the board
/PerFPM-1/Fast Pulse Capture/UNIPOLAR: C218.1, R207.2, R209.2; also elsewhere on the board
/PerFPM-1/Fast Shaper/IN: R192.1; also elsewhere on the board
GND: C208.2, C210.2, C211.2, C212.2, C217.2, C218.2, D26.2 (A), U35.4 (V-), U36.4 (V-); also elsewhere on the board
unnamed: C207.1, R192.2
unnamed: C209.2, R197.1, U35.1
unnamed: C211.1, R196.2, R197.2, R198.1
unnamed: C213.2, R201.2, R202.1, R204.1, U35.7
unnamed: C214.1, R202.2
unnamed: C215.2, R208.1, U36.7
unnamed: C216.2, R209.1, U36.1
unnamed: C207.2, D25.2 (A), D26.1 (K), R193.1
unnamed: R194.2, U35.3 (+)
unnamed: C209.1, R193.2, R196.1, U35.2 (-)
unnamed: R198.2, U35.5 (+)
unnamed: C213.1, R199.2, R201.1, U35.6 (-)
unnamed: C210.1, R195.2, U35.8 (V+)
unnamed: R205.2, U36.3 (+)
unnamed: C216.1, R204.2, R207.1, U36.2 (-)
unnamed: R203.2, U36.5 (+)
unnamed: C214.2, C215.1, R206.1, U36.6 (-)
unnamed: C212.1, R200.2, U36.8 (V+)
VHS: C208.1, R194.1, R199.1, R203.1, R205.1; also elsewhere on the board

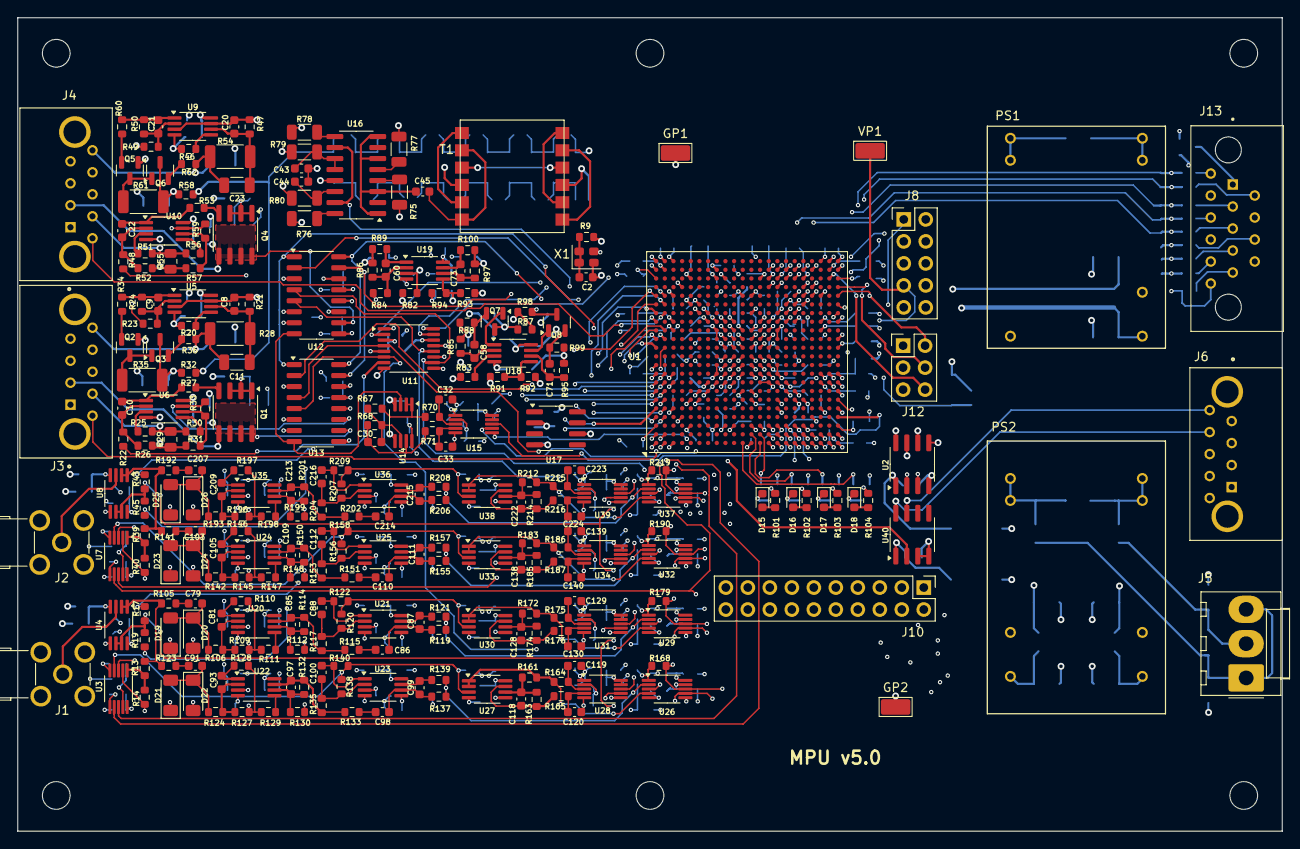
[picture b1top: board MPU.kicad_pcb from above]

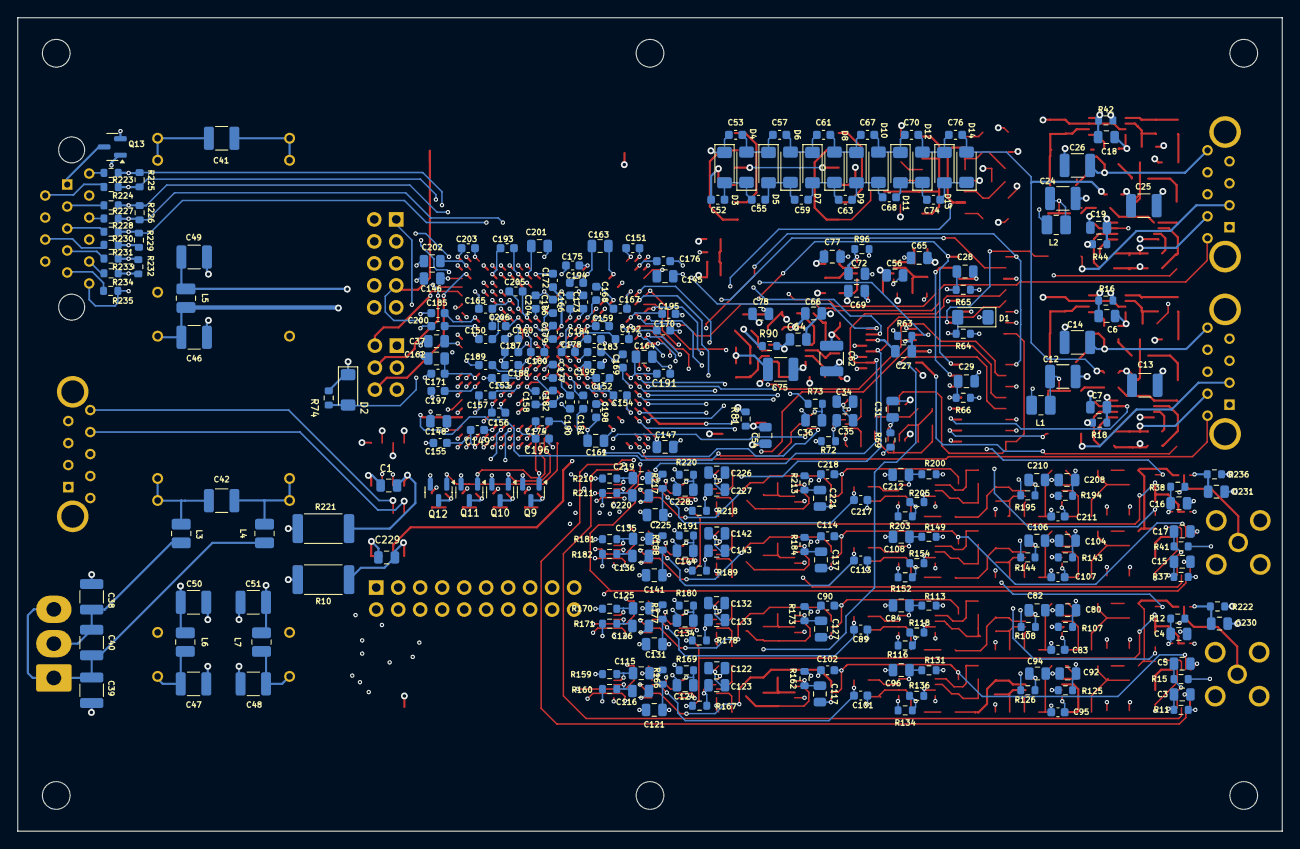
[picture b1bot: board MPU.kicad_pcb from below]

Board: 6 copper layers, 146.1 x 94.0 mm, 562 parts (284 on the bottom side), 378 nets.

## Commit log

2024-03-30 Initial checkin
2024-03-30 Relative path for title
2024-04-15 separate boards for detector and preamp
2024-04-15 more rel paths
2024-05-24 more transcription
2024-05-25 All pages populated with parts
2024-05-25 Passes DRC
2024-05-26 CL resistor for RS422
2024-05-28 bunch of little fixes
2024-05-28 Better names
2024-05-29 Better page order
2024-06-05 Review Release 1
2024-06-12 start work on chain simulation
2024-06-12 MXS interface
2024-06-20 LVDS I/F for HV
2024-06-28 PPS is RS422, add MXINH
2024-07-10 Fix errors found by Norm Dobson
2024-07-10 Fix errors found by Norm Dobson (really)
2024-10-04 Values for TBD caps
2025-02-05 separate detector, preamp
2025-02-17 Kicad update rewrote files
2025-02-17 sim snapshot
2025-02-17 made some changes
2025-02-17 Pulse buffer power fix. HV reg compensation fix.
2025-02-17 trying to get a stable sim
2025-02-17 fast chain sim
2025-02-17 try with ngspice
2025-02-17 fix diode model
2025-02-17 almost working with ltspice
2025-02-18 exported netlist works with ngspice
2025-02-18 balance fast shaper
2025-02-19 fix MPU temp sensor bias
2025-02-19 simulation makefile
2025-02-25 Kicad 9
2025-06-30 enhance .gitignores
2025-06-30 Files changed due to KiCAD update
2025-07-12 S/H for fast channel. Higher HV.
2025-07-12 Simplify fast capture logic
2025-07-16 Commit ICD
2025-07-17 new acq timing diagram
2025-08-02 HV generation based on bench testing
2025-09-02 more prep for new FPGA
2025-09-02 component values for 150 ns fast shaping
2025-09-03 remove unneeded debug connectors
2025-09-03 update rev and date
2025-09-04 ICD changes from HV branch
2025-09-13 Chainsim working, a little tuneup
2025-09-13 tweak shaper caps based on sim
2025-09-18 begin work on schem doc
2025-09-22 revert cap changes from sim. Don't trust it...
2025-09-22 remove Spacewire I/F
2025-09-22 layout release 1
2025-10-15 more work on schem doc
2025-12-03 Fix symbols for release
2025-12-03 Releasable schem doc
2025-12-03 update date and rev
2025-12-11 add missing footprints
2026-03-24 PCB layout from Joel
